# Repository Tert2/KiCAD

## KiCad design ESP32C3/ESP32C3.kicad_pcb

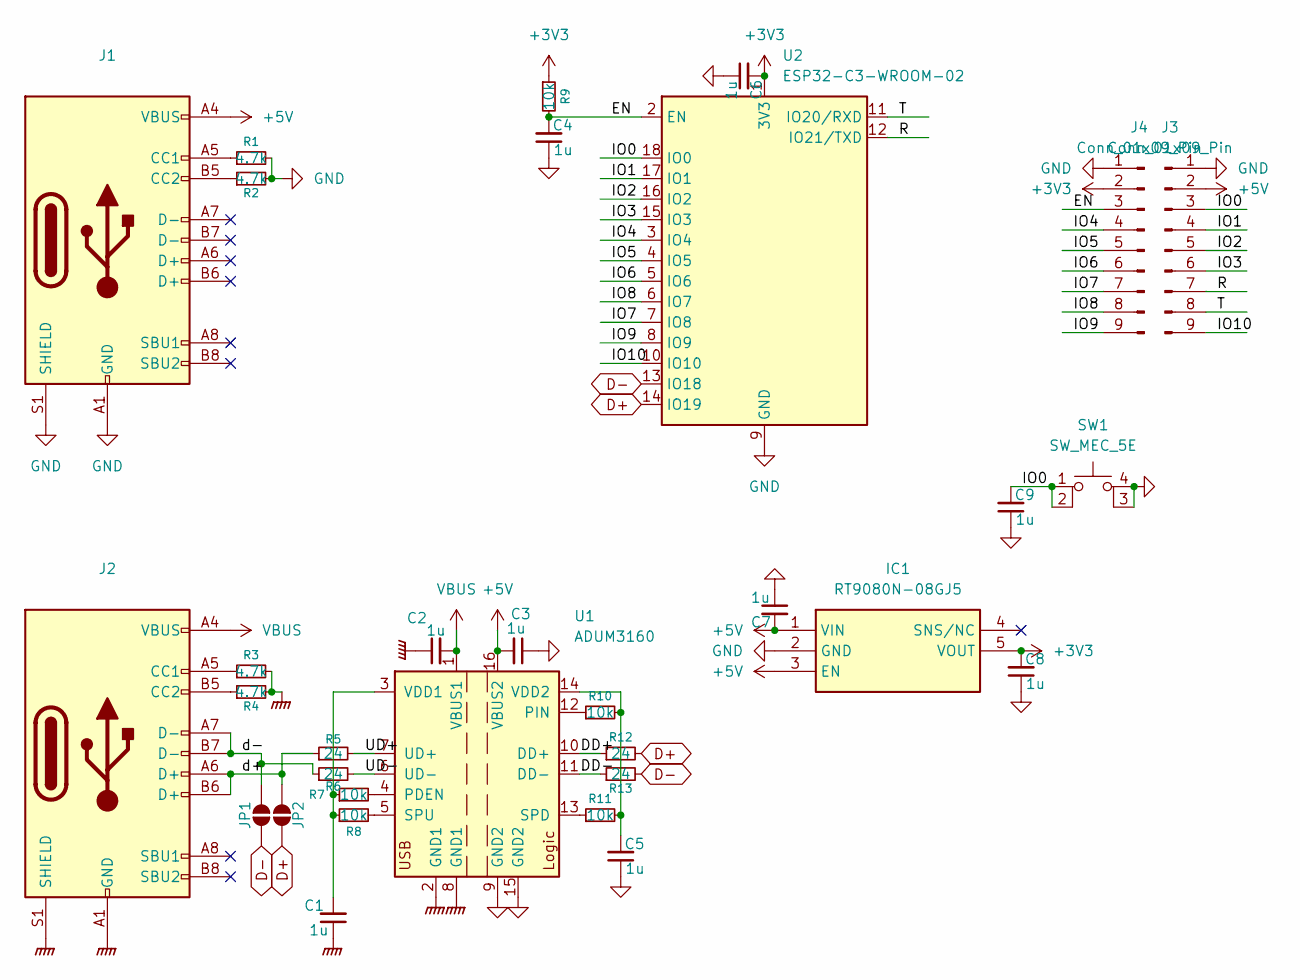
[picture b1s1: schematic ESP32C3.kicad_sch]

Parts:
C1, C2, C3, C4, C5, C6, C7, C8, C9: 1u; C_0603_1608Metric
IC1: RT9080N-08GJ5; SOT94P280X100-5N; Manufacturer_Part_Number RT9080N-08GJ5; Mouser Part Number 835-RT9080N-08GJ5
J1, J2: USB_C_Receptacle_USB2.0_16P; USB_C_Receptacle_GCT_USB4105-xx-A_16P_TopMnt_Horizontal
J3, J4: Conn_01x09_Pin; PinHeader_1x09_P2.54mm_Vertical
JP1, JP2: SolderJumper_2_Open; SolderJumper-2_P1.3mm_Open_RoundedPad1.0x1.5mm
R1, R2, R3, R4: 4.7k; R_0603_1608Metric
R5, R6, R12, R13: 24; R_0603_1608Metric
R7, R8, R9, R10, R11: 10k; R_0603_1608Metric
SW1: SW_MEC_5E; SW_SKRPABE010
U1: ADUM3160; SOIC-16W_7.5x10.3mm_P1.27mm
U2: ESP32-C3-WROOM-02

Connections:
+3V3: C6.2, C8.2, IC1.5 (VOUT), J4.2, R9.1, U2.1 (3V3)
+5V: C3.2, C7.2, IC1.1 (VIN), IC1.3 (EN), J1.A4 (VBUS), J1.A9 (VBUS), J1.B4 (VBUS), J1.B9 (VBUS), J3.2, U1.16 (VBUS2)
/DD+: R12.1, U1.10 (DD+)
/DD-: R13.1, U1.11 (DD-)
/EN: C4.2, J4.3, R9.2, U2.2 (EN)
/IO0: C9.2, J3.3, SW1.1, SW1.2, U2.18 (IO0)
/IO1: J3.4, U2.17 (IO1)
/IO2: J3.5, U2.16 (IO2)
/IO3: J3.6, U2.15 (IO3)
/IO4: J4.4, U2.3 (IO4)
/IO5: J4.5, U2.4 (IO5)
/IO6: J4.6, U2.5 (IO6)
/IO7: J4.7, U2.7 (IO8)
/IO8: J4.8, U2.6 (IO7)
/IO9: J4.9, U2.8 (IO9)
/IO10: J3.9, U2.10 (IO10)
/R: J3.7, U2.12 (IO21/TXD)
/T: J3.8, U2.11 (IO20/RXD)
/UD+: R5.2, U1.7 (UD+)
/UD-: R6.2, U1.6 (UD-)
/d+: J2.A6 (D+), J2.B6 (D+), JP2.1 (A), R5.1
/d-: J2.A7 (D-), J2.B7 (D-), JP1.1 (A), R6.1
D+: JP2.2 (B), R12.2, U2.14 (IO19)
D-: JP1.2 (B), R13.2, U2.13 (IO18)
GND: C3.1, C4.1, C5.1, C6.1, C7.1, C8.1, C9.1, IC1.2 (GND), J1.A1 (GND), J1.A12 (GND), J1.B1 (GND), J1.B12 (GND), J1.S1 (SHIELD), J3.1, J4.1, R1.2, R2.2, SW1.3 (K), SW1.4 (A), U1.9 (GND2), U1.15 (GND2), U2.9 (GND), U2.19 (GND)
GNDPWR: C1.1, C2.1, J2.A1 (GND), J2.A12 (GND), J2.B1 (GND), J2.B12 (GND), J2.S1 (SHIELD), R3.2, R4.2, U1.2 (GND1), U1.8 (GND1)
unnamed: J1.A5 (CC1), R1.1
unnamed: J1.B5 (CC2), R2.1
unnamed: J2.A5 (CC1), R3.1
unnamed: J2.B5 (CC2), R4.1
unnamed: R7.2, U1.4 (PDEN)
unnamed: R10.1, U1.12 (PIN)
unnamed: R11.1, U1.13 (SPD)
unnamed: R8.2, U1.5 (SPU)
unnamed: C1.2, R7.1, R8.1, U1.3 (VDD1)
unnamed: C5.2, R10.2, R11.2, U1.14 (VDD2)
VBUS: C2.2, J2.A4 (VBUS), J2.A9 (VBUS), J2.B4 (VBUS), J2.B9 (VBUS), U1.1 (VBUS1)

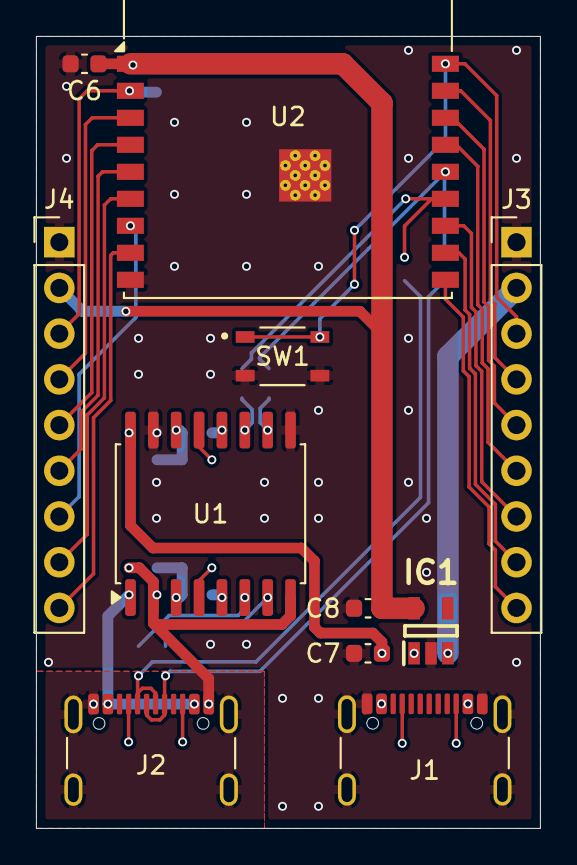
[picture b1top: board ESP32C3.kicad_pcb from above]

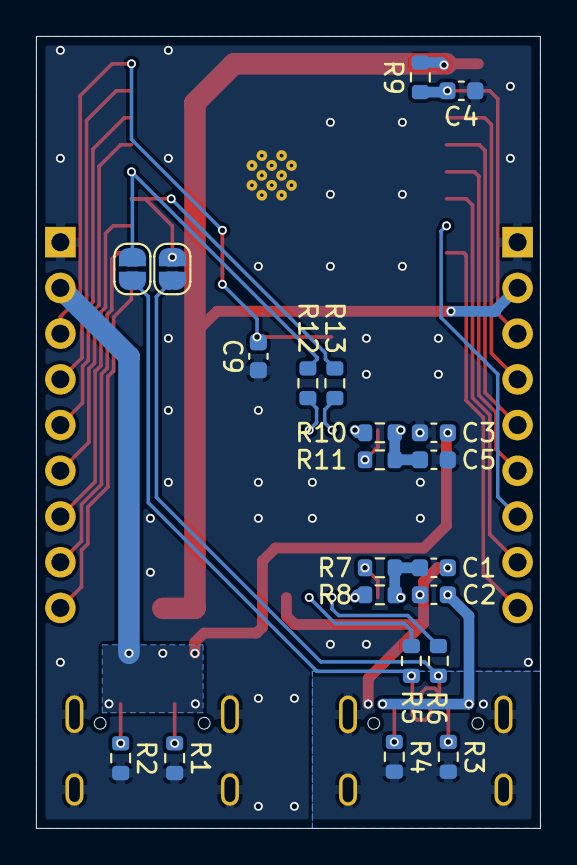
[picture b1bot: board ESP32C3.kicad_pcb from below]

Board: 2 copper layers, 28.0 x 44.0 mm, 32 parts (21 on the bottom side), 37 nets.

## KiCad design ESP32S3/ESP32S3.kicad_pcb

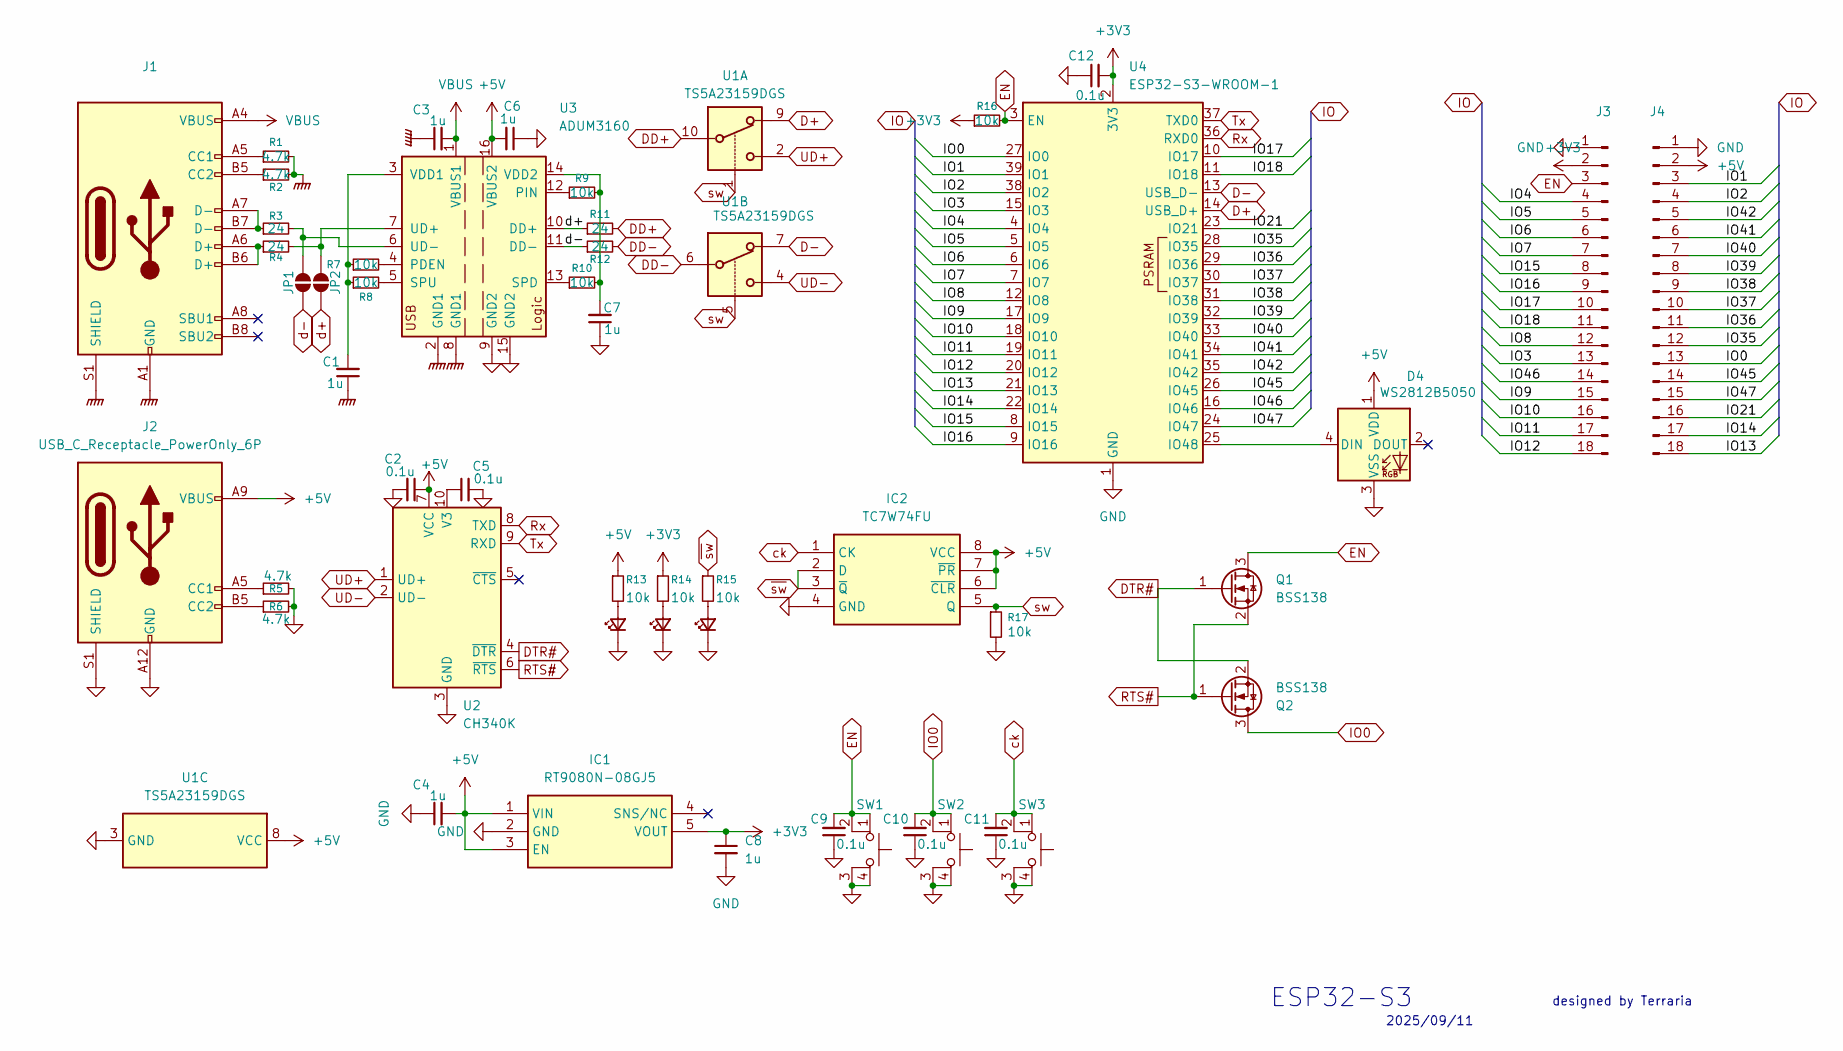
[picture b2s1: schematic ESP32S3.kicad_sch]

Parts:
C1, C3, C4, C6, C7, C8: 1u; C_0603_1608Metric
C2, C5: 0.1u; C_0603_1608Metric_Pad1.08x0.95mm_HandSolder
C9, C10, C11, C12: 0.1u; C_0603_1608Metric
D1, D2, D3: LED_Small; LED_0603_1608Metric_Pad1.05x0.95mm_HandSolder
D4: WS2812B5050; LED_WS2812B_PLCC4_5.0x5.0mm_P3.2mm
IC1: RT9080N-08GJ5; SOT94P280X100-5N; Manufacturer_Part_Number RT9080N-08GJ5; Mouser Part Number 835-RT9080N-08GJ5
IC2: TC7W74FU; TC7W53FUF; Manufacturer_Part_Number TC7W74FU; Mouser Part Number N/A
J1: USB_C_Receptacle_USB2.0_16P; USB_C_Receptacle_GCT_USB4105-xx-A_16P_TopMnt_Horizontal
J2: USB_C_Receptacle_PowerOnly_6P; USB_C_Receptacle_GCT_USB4125-xx-x_6P_TopMnt_Horizontal
J3, J4: Conn_01x18_Pin; PinHeader_1x18_P2.54mm_Vertical
JP1, JP2: SolderJumper_2_Open; SolderJumper-2_P1.3mm_Open_RoundedPad1.0x1.5mm
Q1, Q2: BSS138; SOT-23
R1, R2: 4.7k; R_0603_1608Metric
R3, R4, R11, R12: 24; R_0603_1608Metric
R5, R6: 4.7k; R_0603_1608Metric_Pad0.98x0.95mm_HandSolder
R7, R8, R9, R10, R16: 10k; R_0603_1608Metric
R13, R14, R15, R17: 10k; R_0603_1608Metric_Pad0.98x0.95mm_HandSolder
SW1, SW2, SW3: SW_MEC_5E; SW_SKRPABE010
U1: TS5A23159DGS; VSSOP-10_3x3mm_P0.5mm
U2: CH340K; SSOP-10-1EP_3.9x4.9mm_P1mm_EP2.1x3.3mm
U3: ADUM3160; SOIC-16W_7.5x10.3mm_P1.27mm
U4: ESP32-S3-WROOM-1

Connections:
+3V3: C8.1, C12.2, IC1.5 (VOUT), J3.2, R14.1, R16.1, U4.2 (3V3)
+5V: C2.1, C4.2, C6.2, D4.1 (VDD), IC1.1 (VIN), IC1.3 (EN), IC2.6 (~CLR), IC2.7 (~PR), IC2.8 (VCC), J2.A9 (VBUS), J2.B9 (VBUS), J4.2, R13.1, U1.8 (VCC), U2.7 (VCC), U3.16 (VBUS2)
/IO1: J4.3, U4.39 (IO1)
/IO2: J4.4, U4.38 (IO2)
/IO3: J3.13, U4.15 (IO3)
/IO4: J3.4, U4.4 (IO4)
/IO5: J3.5, U4.5 (IO5)
/IO6: J3.6, U4.6 (IO6)
/IO7: J3.7, U4.7 (IO7)
/IO8: J3.12, U4.12 (IO8)
/IO9: J3.15, U4.17 (IO9)
/IO10: J3.16, U4.18 (IO10)
/IO11: J3.17, U4.19 (IO11)
/IO12: J3.18, U4.20 (IO12)
/IO13: J4.18, U4.21 (IO13)
/IO14: J4.17, U4.22 (IO14)
/IO15: J3.8, U4.8 (IO15)
/IO16: J3.9, U4.9 (IO16)
/IO17: J3.10, U4.10 (IO17)
/IO18: J3.11, U4.11 (IO18)
/IO21: J4.16, U4.23 (IO21)
/IO35: J4.12, U4.28 (IO35)
/IO36: J4.11, U4.29 (IO36)
/IO37: J4.10, U4.30 (IO37)
/IO38: J4.9, U4.31 (IO38)
/IO39: J4.8, U4.32 (IO39)
/IO40: J4.7, U4.33 (IO40)
/IO41: J4.6, U4.34 (IO41)
/IO42: J4.5, U4.35 (IO42)
/IO45: J4.14, U4.26 (IO45)
/IO46: J3.14, U4.16 (IO46)
/IO47: J4.15, U4.24 (IO47)
D+: U1.9, U4.14 (USB_D+)
D-: U1.7, U4.13 (USB_D-)
DD+: R11.2, U1.10
DD-: R12.2, U1.6
DTR#: Q1.1 (G), Q2.2 (S), U2.4 (~DTR)
EN: C9.2, J3.3, Q1.3 (D), R16.2, SW1.1, SW1.2, U4.3 (EN)
GND: C2.2, C4.1, C5.2, C6.1, C7.1, C8.2, C9.1, C10.1, C11.1, C12.1, D1.1 (K), D2.1 (K), D3.1 (K), D4.3 (VSS), IC1.2 (GND), IC2.4 (GND), J2.A12 (GND), J2.B12 (GND), J2.S1 (SHIELD), J3.1, J4.1, R5.2, R6.2, R17.2, SW1.3 (K), SW1.4 (A), SW2.3 (K), SW2.4 (A), SW3.3 (K), SW3.4 (A), U1.3 (GND), U2.3 (GND), U2.11 (GND), U3.9 (GND2), U3.15 (GND2), U4.1 (GND), U4.40 (GND), U4.41 (GND)
GNDPWR: C1.1, C3.1, J1.A1 (GND), J1.A12 (GND), J1.B1 (GND), J1.B12 (GND), J1.S1 (SHIELD), R1.2, R2.2, U3.2 (GND1), U3.8 (GND1)
IO0: C10.2, J4.13, Q2.3 (D), SW2.1, SW2.2, U4.27 (IO0)
unnamed: D1.2 (A), R13.2
unnamed: D2.2 (A), R14.2
unnamed: D3.2 (A), R15.2
unnamed: D4.4 (DIN), U4.25 (IO48)
unnamed: J1.A5 (CC1), R1.1
unnamed: J1.B5 (CC2), R2.1
unnamed: J1.A6 (D+), J1.B6 (D+), R4.1
unnamed: J1.A7 (D-), J1.B7 (D-), R3.1
unnamed: J2.A5 (CC1), R5.1
unnamed: J2.B5 (CC2), R6.1
unnamed: JP1.1 (A), R3.2, U3.6 (UD-)
unnamed: JP2.1 (A), R4.2, U3.7 (UD+)
unnamed: C5.1, U2.10 (V3)
unnamed: R7.2, U3.4 (PDEN)
unnamed: R9.1, U3.12 (PIN)
unnamed: R10.1, U3.13 (SPD)
unnamed: R8.2, U3.5 (SPU)
unnamed: C1.2, R7.1, R8.1, U3.3 (VDD1)
unnamed: C7.2, R9.2, R10.2, U3.14 (VDD2)
RTS#: Q1.2 (S), Q2.1 (G), U2.6 (~RTS)
Rx: U2.8 (TXD), U4.36 (RXD0)
Tx: U2.9 (RXD), U4.37 (TXD0)
UD+: U1.2, U2.1 (UD+)
UD-: U1.4, U2.2 (UD-)
VBUS: C3.2, J1.A4 (VBUS), J1.A9 (VBUS), J1.B4 (VBUS), J1.B9 (VBUS), U3.1 (VBUS1)
ck: C11.2, IC2.1 (CK), SW3.1, SW3.2
d+: JP2.2 (B), R11.1, U3.10 (DD+)
d-: JP1.2 (B), R12.1, U3.11 (DD-)
sw: IC2.5 (Q), R17.1, U1.1, U1.5
~sw: IC2.2 (D), IC2.3 (~Q), R15.1

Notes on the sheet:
ESP32-S3
2025/09/11
designed by Terraria

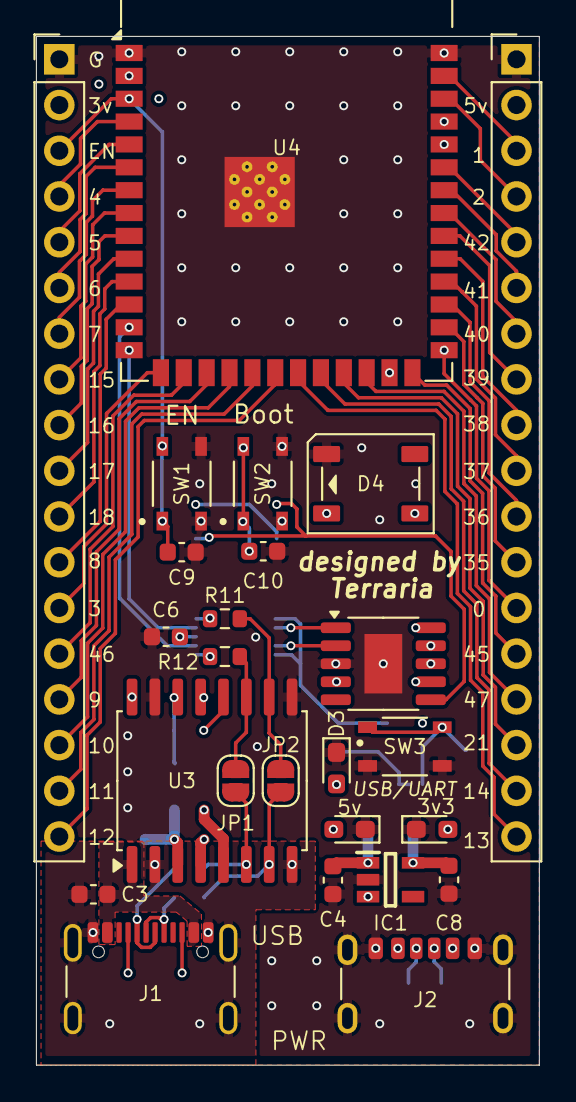
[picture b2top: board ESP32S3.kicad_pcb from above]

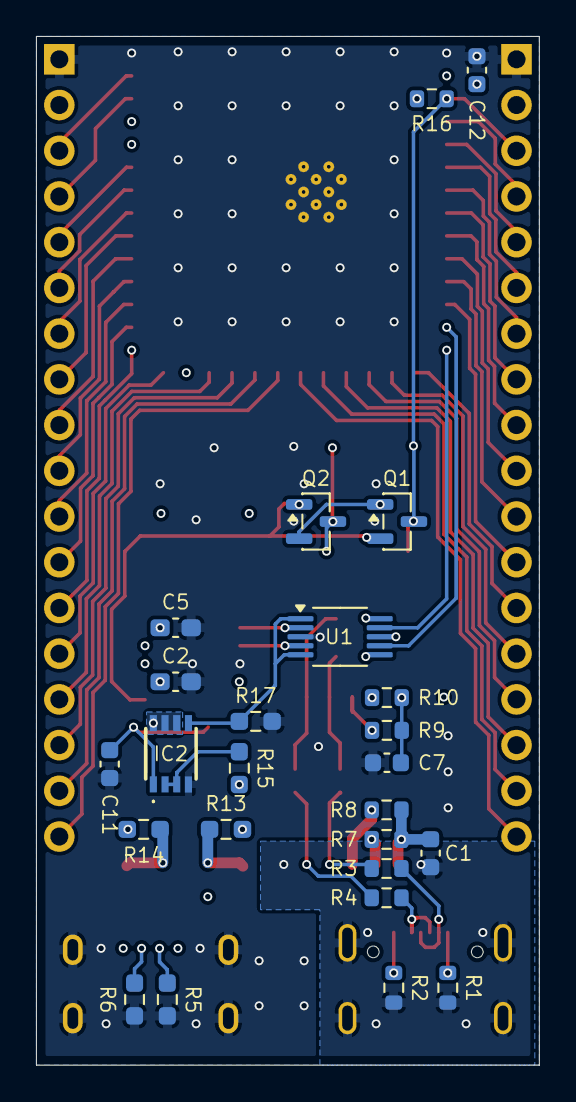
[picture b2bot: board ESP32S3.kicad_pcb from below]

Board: 4 copper layers, 27.9 x 57.1 mm, 50 parts (25 on the bottom side), 71 nets.

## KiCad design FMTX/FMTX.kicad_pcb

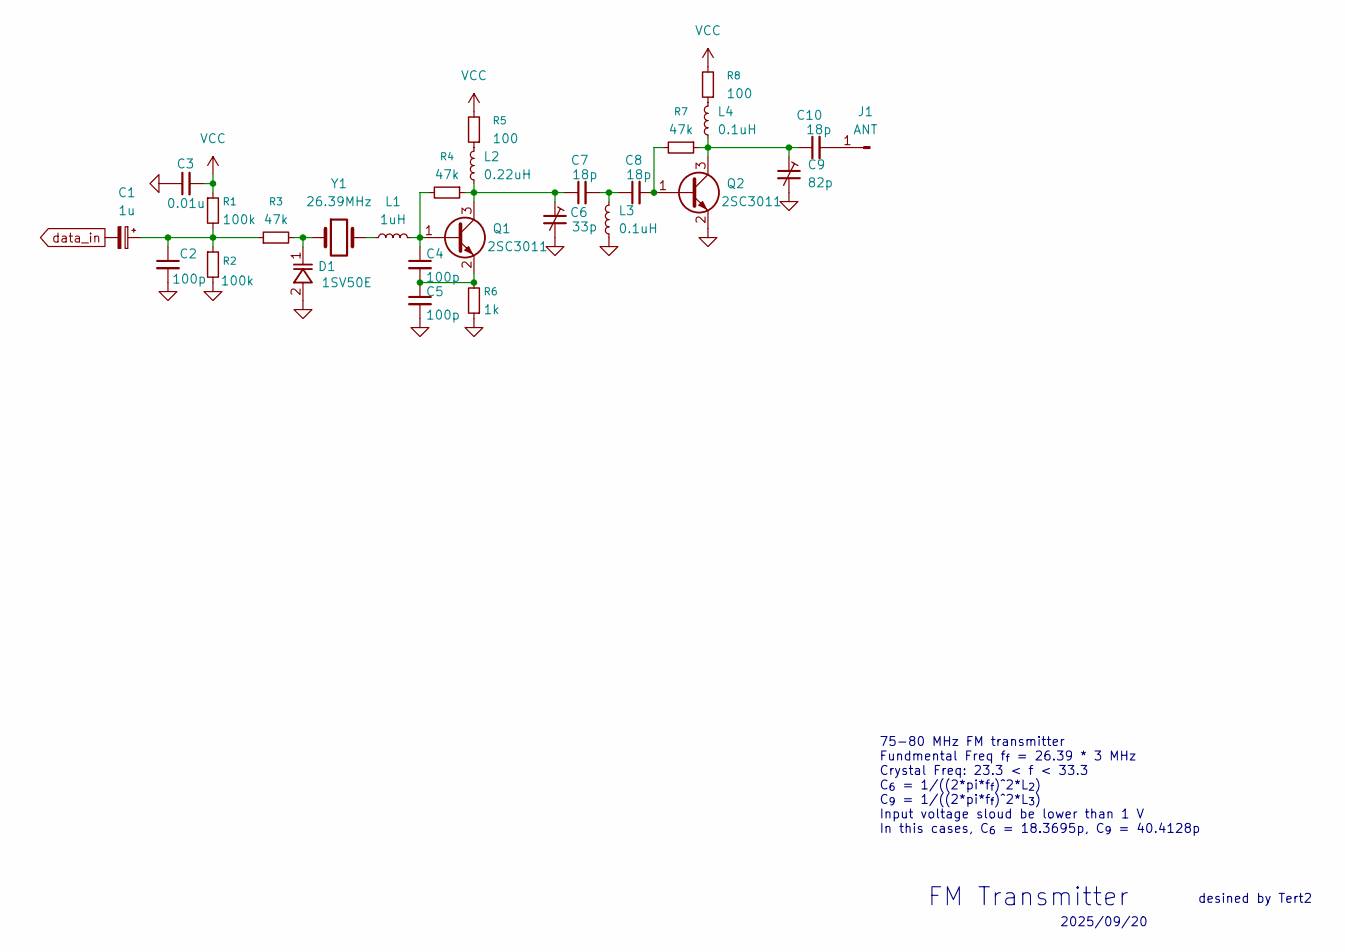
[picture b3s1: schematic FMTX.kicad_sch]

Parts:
C1: 1u; CP_Radial_D5.0mm_P2.00mm
C2, C4, C5: 100p; C_0603_1608Metric
C3: 0.01u; C_0603_1608Metric
C6: 33p; C_Radial_D10.0mm_H16.0mm_P5.00mm
C7, C8, C10: 18p; C_0603_1608Metric
C9: 82p; C_Radial_D10.0mm_H16.0mm_P5.00mm
D1: 1SV50E; D_A-405_P7.62mm_Horizontal
J1: ANT; PinHeader_1x01_P2.54mm_Vertical
L1: 1uH; C_0805_2012Metric
L2: 0.22uH; C_0805_2012Metric
L3, L4: 0.1uH; C_0805_2012Metric
Q1, Q2: 2SC3011; TSOT-23
R1, R2: 100k; R_0603_1608Metric
R3, R4, R7: 47k; R_0603_1608Metric
R5, R8: 100; R_0603_1608Metric
R6: 1k; R_0603_1608Metric
Y1: 26.39MHz; Crystal_HC18-U_Vertical

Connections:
GND: C2.2, C3.1, C5.2, C6.2, C9.2, D1.2, L3.1, Q2.2 (E), R2.2, R6.1
unnamed: C1.1, C2.1, R1.2, R2.1, R3.1
unnamed: C7.2, C8.1, L3.2
unnamed: D1.1, R3.2, Y1.1
unnamed: C10.2, J1.1
unnamed: L1.1, Y1.2
unnamed: L2.2, R5.1
unnamed: L4.2, R8.1
unnamed: C4.1, L1.2, Q1.1 (B), R4.2
unnamed: C6.1, C7.1, L2.1, Q1.3 (C), R4.1
unnamed: C4.2, C5.1, Q1.2 (E), R6.2
unnamed: C8.2, Q2.1 (B), R7.2
unnamed: C9.1, C10.1, L4.1, Q2.3 (C), R7.1
VCC: C3.2, R1.1, R5.2, R8.2
data_in: C1.2

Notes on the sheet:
2025/09/20
FM Transmitter
desined by Tert2
75-80 MHz FM transmitter Fundmental Freq f_{f} = 26.39 * 3 MHz Crystal Freq: 23.3 < f < 33.3 C_{6} = 1/((2*pi*f_{f})^2*L_{2}) C_{9} = 1/((2*pi*f_{f})^2*L_{3}) Input voltage sloud be lower than 1 V In this cases, C_{6} = 18.3695p, C_{9} = 40.4128p

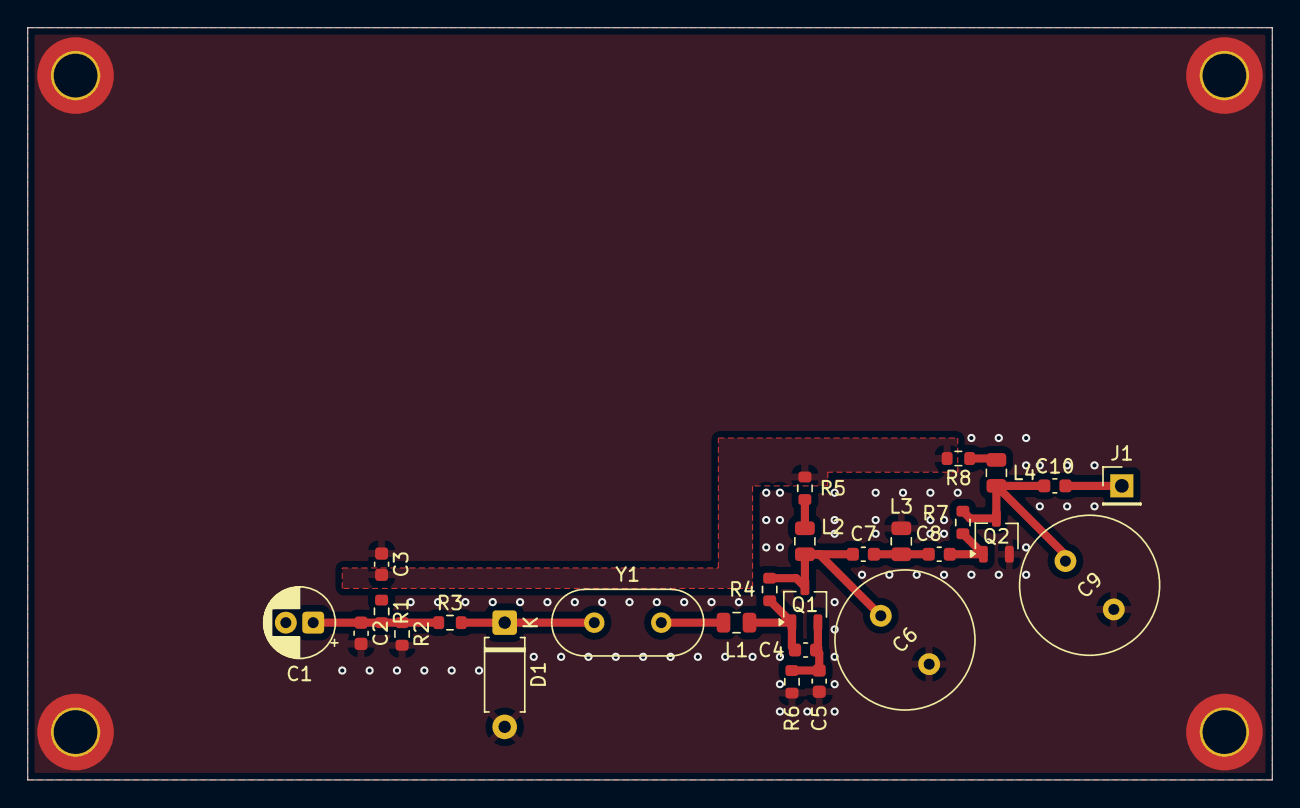
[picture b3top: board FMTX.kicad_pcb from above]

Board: 2 copper layers, 91.0 x 55.0 mm, 27 parts (0 on the bottom side), 14 nets.

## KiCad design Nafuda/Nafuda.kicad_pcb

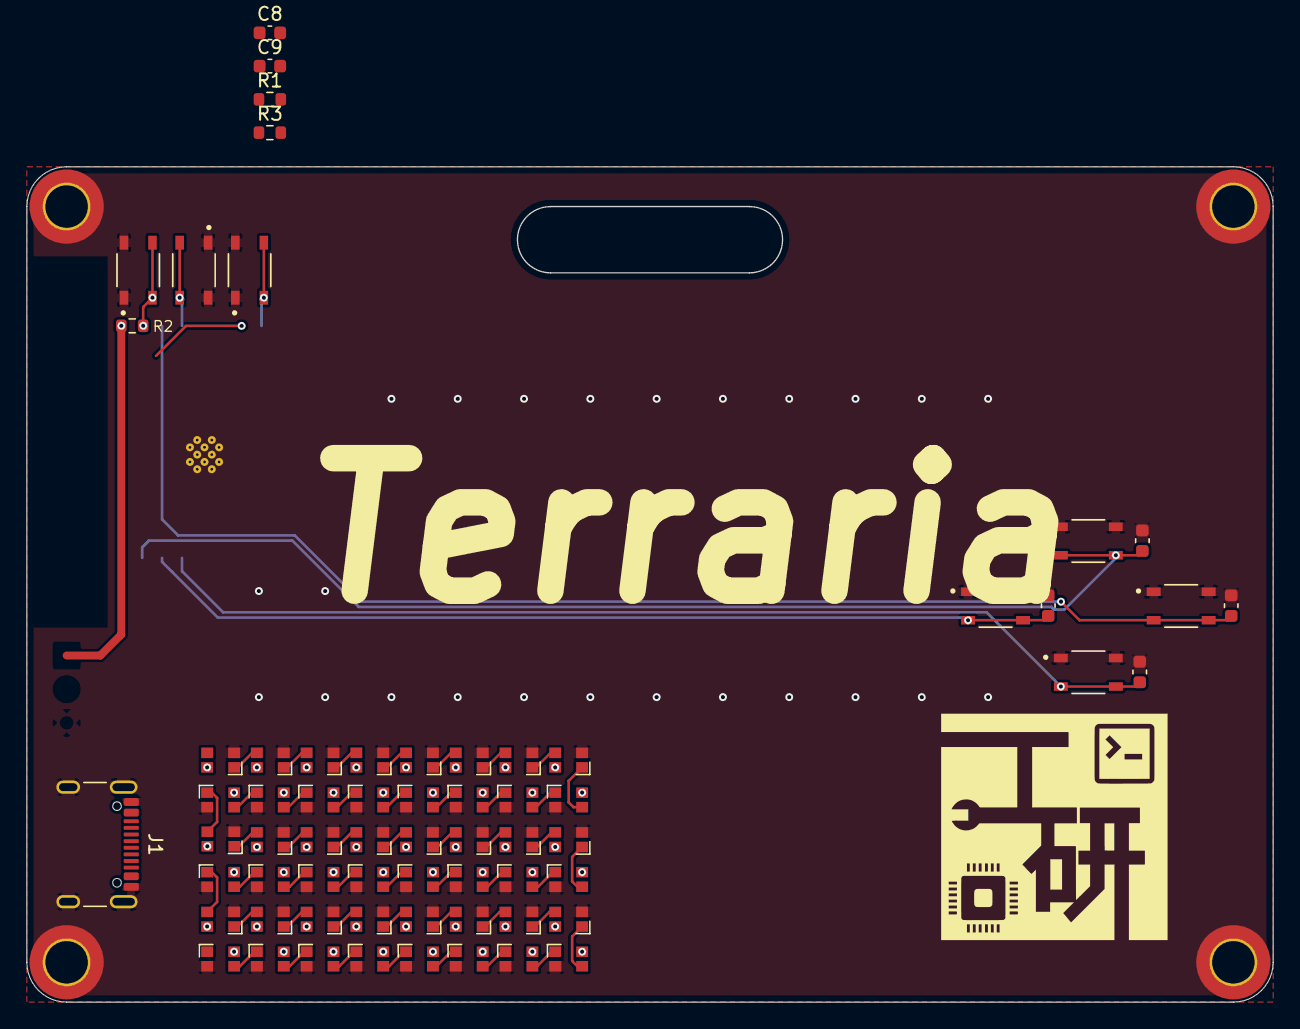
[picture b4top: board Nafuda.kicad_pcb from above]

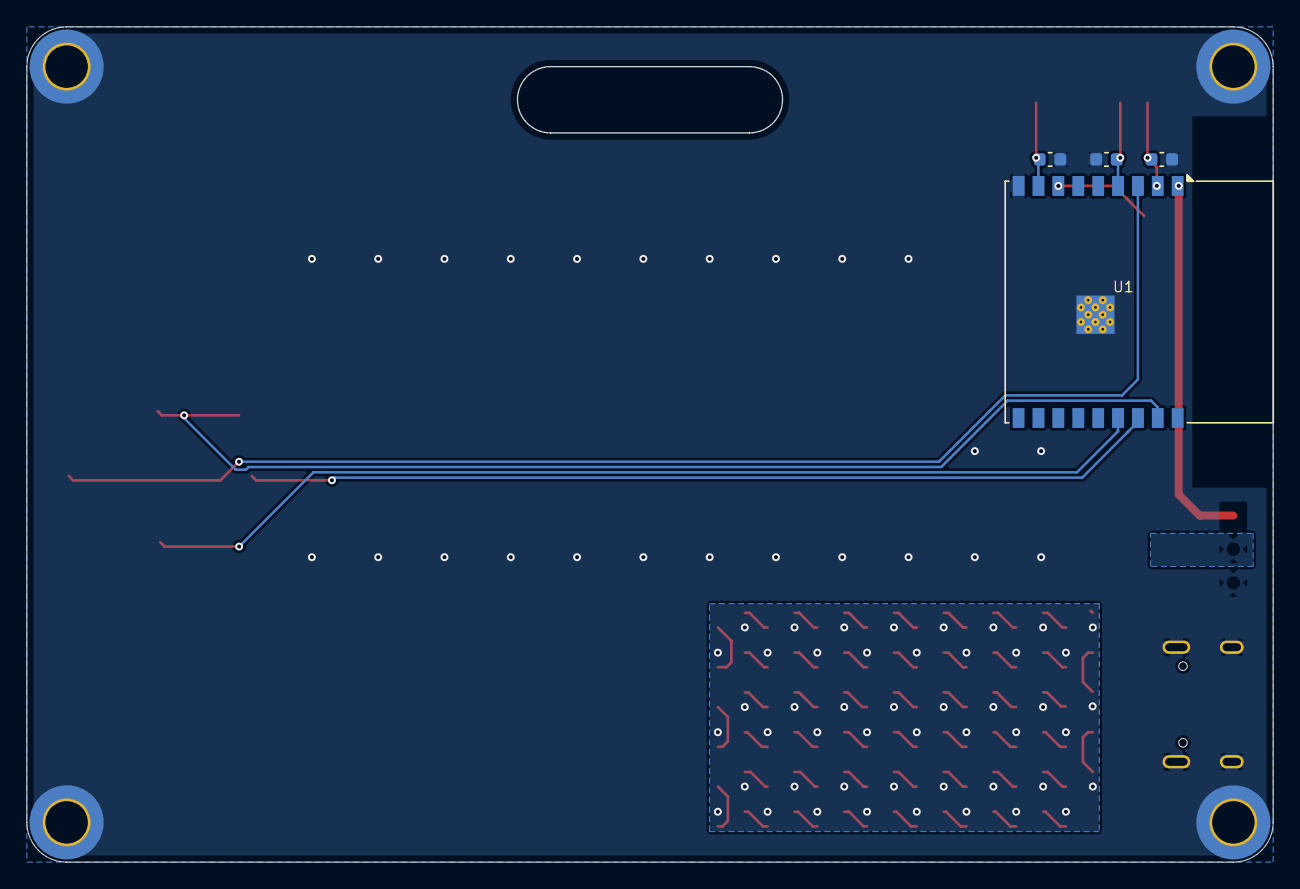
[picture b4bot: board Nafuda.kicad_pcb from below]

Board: 2 copper layers, 94.0 x 63.0 mm, 73 parts (4 on the bottom side), 62 nets.

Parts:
C1, C2, C3, C4, C5, C6, C7, C8, C9: 0.1u; C_0603_1608Metric
D1, D2, D3, D4, D5, D6, D7, D8, D9, D10, D11, D12, D13, D14, D15, D16, D17, D18, D19, D20, D21, D22, D23, D24, D25, D26, D27, D28, D29, D30, D31, D32, D33, D34, D35, D36, D37, D38, D39, D40, D41, D42, D43, D44, D45, D46, D47, D48: WS2812B-2020; ws2812b-2020
J1: USB_C_Receptacle_USB2.0_16P; USB_C_Receptacle_GCT_USB4105-xx-A_16P_TopMnt_Horizontal
J2, J3, J4, J5: Conn_01x01_Pin; MountingHole_3.2mm_M3_DIN965_Pad_TopBottom
R1, R3: 5.1k; R_0603_1608Metric
R2: 10k; R_0603_1608Metric
SW1, SW2, SW3, SW4, SW5, SW6, SW7: SW_MEC_5E; SW_SKRPABE010
U1: ESP32-C3-WROOM-02

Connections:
+3V3: C9.2, R2.1, U1.1 (3V3)
BOOT: C4.2, SW4.3 (K), SW4.4 (A), U1.8 (IO9)
D1: D1.3 (DIN), U1.7 (IO8)
D2: D16.1 (DOUT), D17.3 (DIN)
D3: D32.1 (DOUT), D33.3 (DIN)
D+: J1.A6 (D+), J1.B6 (D+), U1.14 (IO19)
D-: J1.A7 (D-), J1.B7 (D-), U1.13 (IO18)
EN: C7.2, R2.2, SW7.3 (K), SW7.4 (A), U1.2 (EN)
GND: C1.1, C2.1, C3.1, C4.1, C5.1, C6.1, C7.1, C8.1, C9.1, D1.2 (VSS), D2.2 (VSS), D3.2 (VSS), D4.2 (VSS), D5.2 (VSS), D6.2 (VSS), D7.2 (VSS), D8.2 (VSS), D9.2 (VSS), D10.2 (VSS), D11.2 (VSS), D12.2 (VSS), D13.2 (VSS), D14.2 (VSS), D15.2 (VSS), D16.2 (VSS), D17.2 (VSS), D18.2 (VSS), D19.2 (VSS), D20.2 (VSS), D21.2 (VSS), D22.2 (VSS), D23.2 (VSS), D24.2 (VSS), D25.2 (VSS), D26.2 (VSS), D27.2 (VSS), D28.2 (VSS), D29.2 (VSS), D30.2 (VSS), D31.2 (VSS), D32.2 (VSS), D33.2 (VSS), D34.2 (VSS), D35.2 (VSS), D36.2 (VSS), D37.2 (VSS), D38.2 (VSS), D39.2 (VSS), D40.2 (VSS), D41.2 (VSS), D42.2 (VSS), D43.2 (VSS), D44.2 (VSS), D45.2 (VSS), D46.2 (VSS), D47.2 (VSS), D48.2 (VSS), J1.A1 (GND), J1.A12 (GND), J1.B1 (GND), J1.B12 (GND), J1.S1 (SHIELD), J2.1, J3.1, J4.1, J5.1, R1.2, R3.2, SW1.1, SW1.2, SW2.1, SW2.2, SW3.1, SW3.2, SW4.1, SW4.2, SW5.1, SW5.2, SW6.1, SW6.2, SW7.1, SW7.2, U1.9 (GND), U1.19 (GND)
unnamed: D1.1 (DOUT), D2.3 (DIN)
unnamed: D2.1 (DOUT), D3.3 (DIN)
unnamed: D3.1 (DOUT), D4.3 (DIN)
unnamed: D4.1 (DOUT), D5.3 (DIN)
unnamed: D5.1 (DOUT), D6.3 (DIN)
unnamed: D6.1 (DOUT), D7.3 (DIN)
unnamed: D7.1 (DOUT), D8.3 (DIN)
unnamed: D8.1 (DOUT), D9.3 (DIN)
unnamed: D9.1 (DOUT), D10.3 (DIN)
unnamed: D10.1 (DOUT), D11.3 (DIN)
unnamed: D11.1 (DOUT), D12.3 (DIN)
unnamed: D12.1 (DOUT), D13.3 (DIN)
unnamed: D13.1 (DOUT), D14.3 (DIN)
unnamed: D14.1 (DOUT), D15.3 (DIN)
unnamed: D15.1 (DOUT), D16.3 (DIN)
unnamed: D17.1 (DOUT), D18.3 (DIN)
unnamed: D18.1 (DOUT), D19.3 (DIN)
unnamed: D19.1 (DOUT), D20.3 (DIN)
unnamed: D20.1 (DOUT), D21.3 (DIN)
unnamed: D21.1 (DOUT), D22.3 (DIN)
unnamed: D22.1 (DOUT), D23.3 (DIN)
unnamed: D23.1 (DOUT), D24.3 (DIN)
unnamed: D24.1 (DOUT), D25.3 (DIN)
unnamed: D25.1 (DOUT), D26.3 (DIN)
unnamed: D26.1 (DOUT), D27.3 (DIN)
unnamed: D27.1 (DOUT), D28.3 (DIN)
unnamed: D28.1 (DOUT), D29.3 (DIN)
unnamed: D29.1 (DOUT), D30.3 (DIN)
unnamed: D30.1 (DOUT), D31.3 (DIN)
unnamed: D31.1 (DOUT), D32.3 (DIN)
unnamed: D33.1 (DOUT), D34.3 (DIN)
unnamed: D34.1 (DOUT), D35.3 (DIN)
unnamed: D35.1 (DOUT), D36.3 (DIN)
unnamed: D36.1 (DOUT), D37.3 (DIN)
unnamed: D37.1 (DOUT), D38.3 (DIN)
unnamed: D38.1 (DOUT), D39.3 (DIN)
unnamed: D39.1 (DOUT), D40.3 (DIN)
unnamed: D40.1 (DOUT), D41.3 (DIN)
unnamed: D41.1 (DOUT), D42.3 (DIN)
unnamed: D42.1 (DOUT), D43.3 (DIN)
unnamed: D43.1 (DOUT), D44.3 (DIN)
unnamed: D44.1 (DOUT), D45.3 (DIN)
unnamed: D45.1 (DOUT), D46.3 (DIN)
unnamed: D46.1 (DOUT), D47.3 (DIN)
unnamed: D47.1 (DOUT), D48.3 (DIN)
unnamed: J1.A5 (CC1), R1.1
unnamed: J1.B5 (CC2), R3.1
SW1: C1.2, SW1.3 (K), SW1.4 (A), U1.17 (IO1)
SW2: C2.2, SW2.3 (K), SW2.4 (A), U1.16 (IO2)
SW3: C3.2, SW3.3 (K), SW3.4 (A), U1.15 (IO3)
SW4: C5.2, SW5.3 (K), SW5.4 (A), U1.3 (IO4)
SW5: C6.2, SW6.3 (K), SW6.4 (A), U1.4 (IO5)
VBUS: D1.4 (VDD), D2.4 (VDD), D3.4 (VDD), D4.4 (VDD), D5.4 (VDD), D6.4 (VDD), D7.4 (VDD), D8.4 (VDD), D9.4 (VDD), D10.4 (VDD), D11.4 (VDD), D12.4 (VDD), D13.4 (VDD), D14.4 (VDD), D15.4 (VDD), D16.4 (VDD), D17.4 (VDD), D18.4 (VDD), D19.4 (VDD), D20.4 (VDD), D21.4 (VDD), D22.4 (VDD), D23.4 (VDD), D24.4 (VDD), D25.4 (VDD), D26.4 (VDD), D27.4 (VDD), D28.4 (VDD), D29.4 (VDD), D30.4 (VDD), D31.4 (VDD), D32.4 (VDD), D33.4 (VDD), D34.4 (VDD), D35.4 (VDD), D36.4 (VDD), D37.4 (VDD), D38.4 (VDD), D39.4 (VDD), D40.4 (VDD), D41.4 (VDD), D42.4 (VDD), D43.4 (VDD), D44.4 (VDD), D45.4 (VDD), D46.4 (VDD), D47.4 (VDD), D48.4 (VDD), J1.A4 (VBUS), J1.A9 (VBUS), J1.B4 (VBUS), J1.B9 (VBUS)

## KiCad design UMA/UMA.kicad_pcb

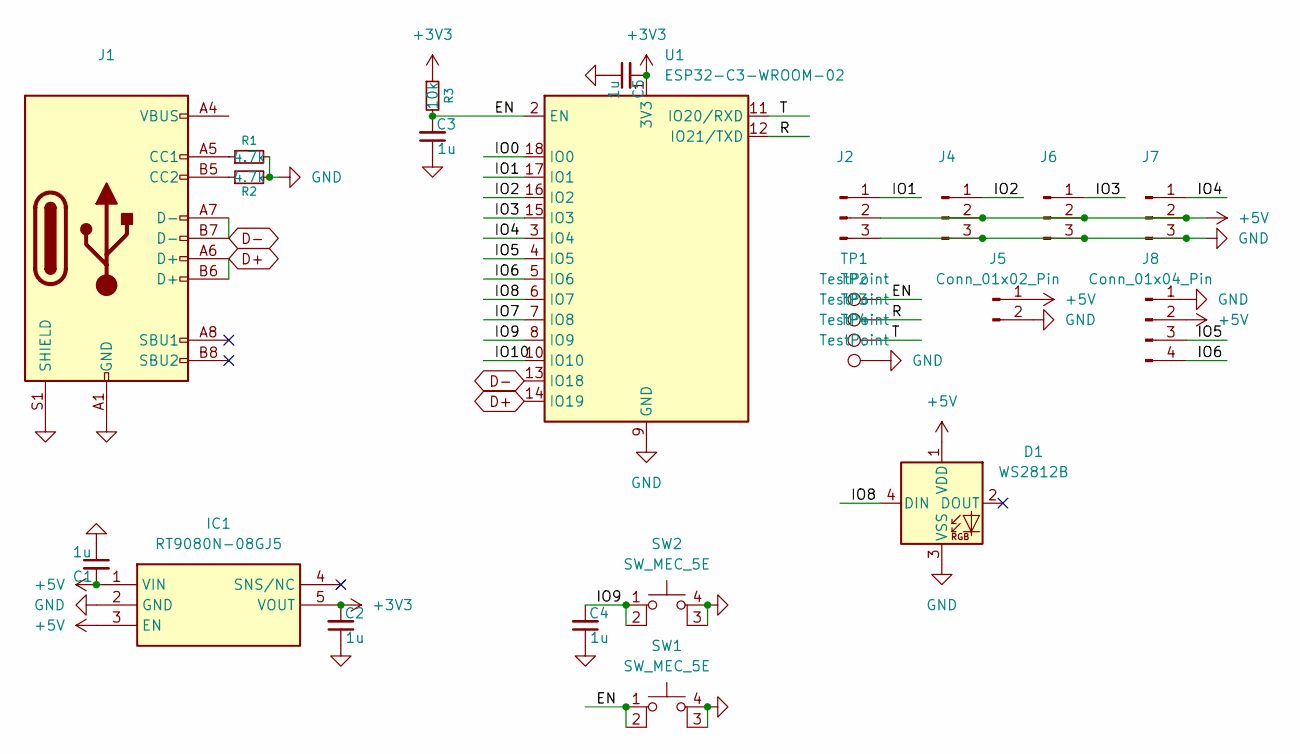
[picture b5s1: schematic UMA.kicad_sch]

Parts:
C1, C2, C3, C4, C5: 1u; C_0603_1608Metric
D1: WS2812B; LED_WS2812B_PLCC4_5.0x5.0mm_P3.2mm
IC1: RT9080N-08GJ5; SOT94P280X100-5N; Manufacturer_Part_Number RT9080N-08GJ5; Mouser Part Number 835-RT9080N-08GJ5
J1: USB_C_Receptacle_USB2.0_16P; USB_C_Receptacle_GCT_USB4105-xx-A_16P_TopMnt_Horizontal
J2, J4, J6, J7: Conn_01x03_Pin; PinHeader_1x03_P2.54mm_Horizontal
J5: Conn_01x02_Pin; JST_XH_S2B-XH-A-1_1x02_P2.50mm_Horizontal
J8: Conn_01x04_Pin; PinHeader_1x04_P2.54mm_Horizontal
R1, R2: 4.7k; R_0603_1608Metric
R3: 10k; R_0603_1608Metric
SW1, SW2: SW_MEC_5E; SW_SKRPABE010
TP1, TP2, TP3, TP4: TestPoint; TestPoint_Pad_D2.0mm
U1: ESP32-C3-WROOM-02

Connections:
+3V3: C2.2, C5.2, IC1.5 (VOUT), R3.1, U1.1 (3V3)
+5V: C1.2, D1.1 (VDD), IC1.1 (VIN), IC1.3 (EN), J2.2, J4.2, J5.1, J6.2, J7.2, J8.2
/EN: C3.2, R3.2, SW1.1, SW1.2, TP1.1, U1.2 (EN)
/IO0: U1.18 (IO0)
/IO1: J2.1, U1.17 (IO1)
/IO2: J4.1, U1.16 (IO2)
/IO3: J6.1, U1.15 (IO3)
/IO4: J7.1, U1.3 (IO4)
/IO5: J8.3, U1.4 (IO5)
/IO6: J8.4, U1.5 (IO6)
/IO7: U1.7 (IO8)
/IO8: D1.4 (DIN), U1.6 (IO7)
/IO9: C4.2, SW2.1, SW2.2, U1.8 (IO9)
/IO10: U1.10 (IO10)
/R: TP2.1, U1.12 (IO21/TXD)
/T: TP3.1, U1.11 (IO20/RXD)
D+: J1.A6 (D+), J1.B6 (D+), U1.14 (IO19)
D-: J1.A7 (D-), J1.B7 (D-), U1.13 (IO18)
GND: C1.1, C2.1, C3.1, C4.1, C5.1, D1.3 (VSS), IC1.2 (GND), J1.A1 (GND), J1.A12 (GND), J1.B1 (GND), J1.B12 (GND), J1.S1 (SHIELD), J2.3, J4.3, J5.2, J6.3, J7.3, J8.1, R1.2, R2.2, SW1.3 (K), SW1.4 (A), SW2.3 (K), SW2.4 (A), TP4.1, U1.9 (GND), U1.19 (GND)
unnamed: J1.A5 (CC1), R1.1
unnamed: J1.B5 (CC2), R2.1
unnamed: J1.A4 (VBUS), J1.A9 (VBUS), J1.B4 (VBUS), J1.B9 (VBUS)

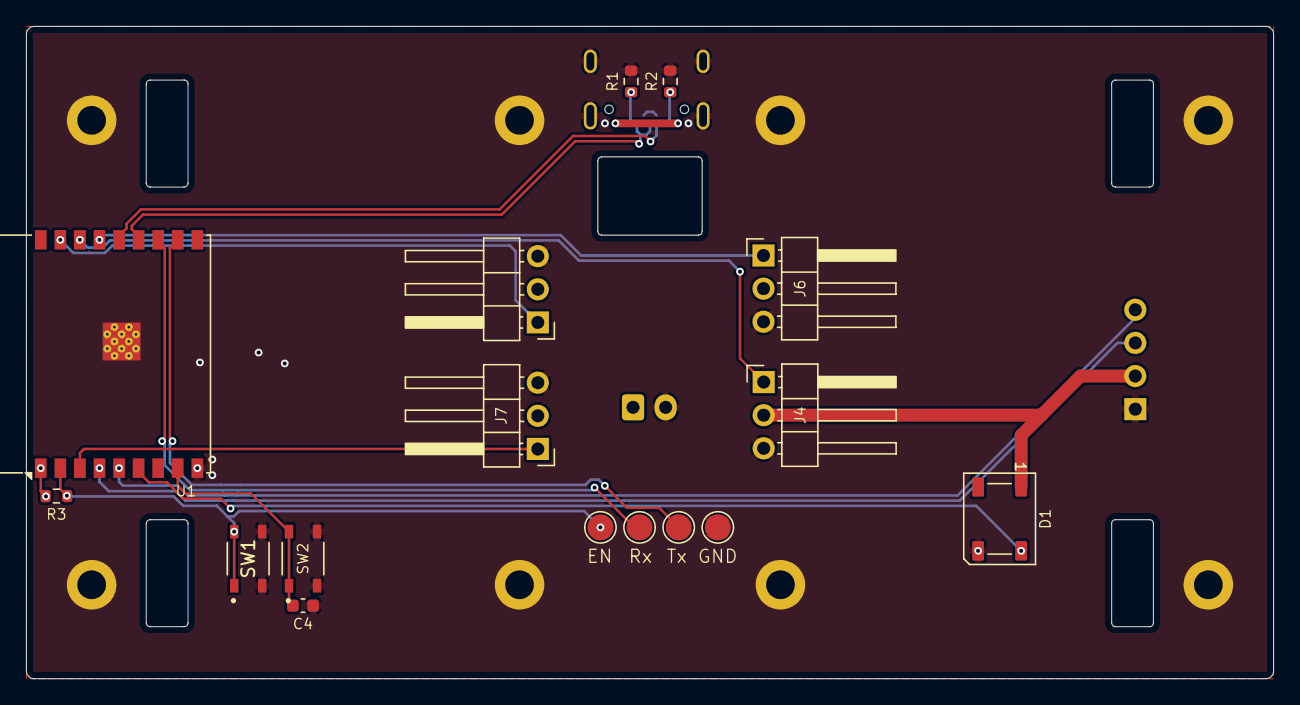
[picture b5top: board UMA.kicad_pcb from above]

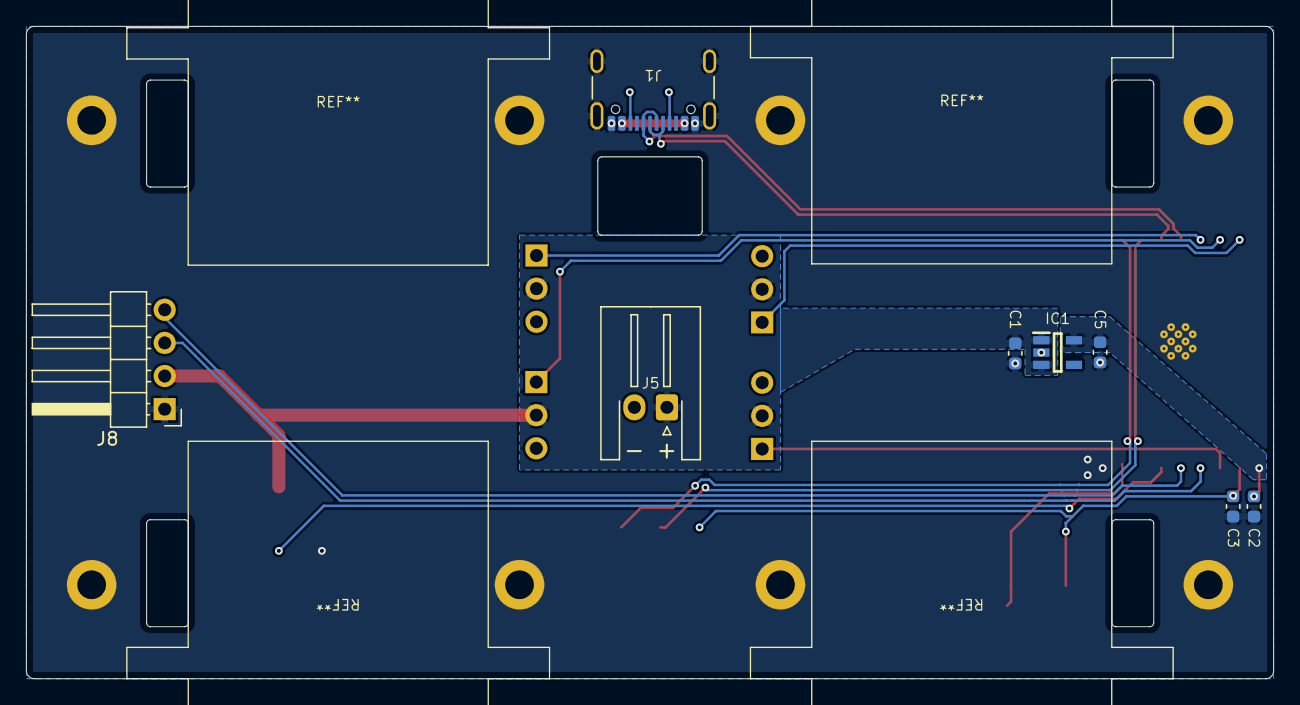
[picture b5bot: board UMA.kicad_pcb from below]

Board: 2 copper layers, 95.6 x 50.0 mm, 24 parts (8 on the bottom side), 19 nets.
